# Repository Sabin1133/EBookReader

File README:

# Proiect Hardware cu ESP32-C6

## Descriere Generală

Acest proiect descrie funcționalitatea hardware a unui sistem bazat pe ESP32-C6, incluzând modulele, componentele și senzorii utilizați, interfețele de conectare, specificațiile de comunicație și calculele de consum de energie.

## Funcționalitate Hardware

### Module și Componente

* **ESP32-C6**: Microcontroller-ul principal, care oferă conectivitate Wi-Fi 6, Bluetooth LE 5.2 și suport pentru protocolul 802.15.4.
* **Senzor de temperatură și umiditate DHT11**: Utilizat pentru monitorizarea condițiilor ambientale.
* **Modul LED RGB**: Pentru afișarea vizuală a stărilor sistemului.
* **Buton tactil**: Pentru interacțiunea utilizatorului.

### Interfețe și Conectivitate

* Senzorul DHT11 este conectat la ESP32-C6 prin interfața GPIO.
* Modulul LED RGB este controlat prin pinii PWM ai ESP32-C6.
* Butonul tactil este conectat la un pin GPIO configurat ca intrare.
* ESP32-C6 comunică prin Wi-Fi pentru a trimite date către un server cloud.

### Specificații de Comunicație

* Wi-Fi 6 (802.11ax): Pentru conectivitate la rețeaua locală și internet.
* Bluetooth LE 5.2: Pentru comunicarea cu dispozitive mobile.
* Protocol 802.15.4: Pentru eventuale comunicații cu dispozitive Zigbee sau Thread.

### Procesare și Calcule

* ESP32-C6 procesează datele de la senzori și controlează modulul LED RGB.
* Se efectuează calcule pentru a converti datele brute ale senzorilor în unități de măsură relevante.
* Calcule de consum de energie.
    * ESP32-C6 în mod activ consumă în jur de 5mA
    * ESP32-C6 în mod sleep consumă în jur de 5µA
    * Senzorul de temperatură și umiditate DHT11 consumă aproximativ 2.5mA.

### Pini ESP32-C6 Utilizați

* **GPIO2 (DHT11 Data)**: Pin de intrare/ieșire pentru comunicarea cu senzorul DHT11.
    * Motiv: GPIO2 suportă interfața de comunicare necesară pentru DHT11.
* **GPIO4 (LED RGB Red)**: Pin PWM pentru controlul componentei roșii a LED-ului RGB.
    * Motiv: GPIO4 suportă PWM, necesar pentru controlul intensității LED-ului.
* **GPIO5 (LED RGB Green)**: Pin PWM pentru controlul componentei verzi a LED-ului RGB.
    * Motiv: GPIO5 suportă PWM, necesar pentru controlul intensității LED-ului.
* **GPIO6 (LED RGB Blue)**: Pin PWM pentru controlul componentei albastre a LED-ului RGB.
    * Motiv: GPIO6 suportă PWM, necesar pentru controlul intensității LED-ului.
* **GPIO7 (Buton tactil)**: Pin de intrare pentru citirea stării butonului tactil.
    * Motiv: GPIO7 poate fi configurat ca intrare digitală pentru a detecta starea butonului.

### Alte Informații Relevante

* Sistemul este alimentat de o baterie de 3.3V.
* Datele colectate sunt trimise către un server cloud pentru monitorizare și analiză.
* Codul sursă este disponibil în directorul `src`.

## Dependențe

* Biblioteca Adafruit DHT pentru comunicarea cu senzorul DHT11.
* Biblioteca Arduino pentru controlul pinilor GPIO și PWM.

## Instalare

1.  Clonați acest repository.
2.  Instalați bibliotecile necesare în Arduino IDE.
3.  Încărcați codul pe ESP32-C6.

## Utilizare

* Sistemul monitorizează temperatura și umiditatea și afișează valorile prin LED-ul RGB.
* Utilizatorul poate interacționa cu sistemul prin intermediul butonului tactil.

## Contribuție

Contribuțiile sunt binevenite! Vă rugăm să trimiteți pull requests sau să raportați probleme.

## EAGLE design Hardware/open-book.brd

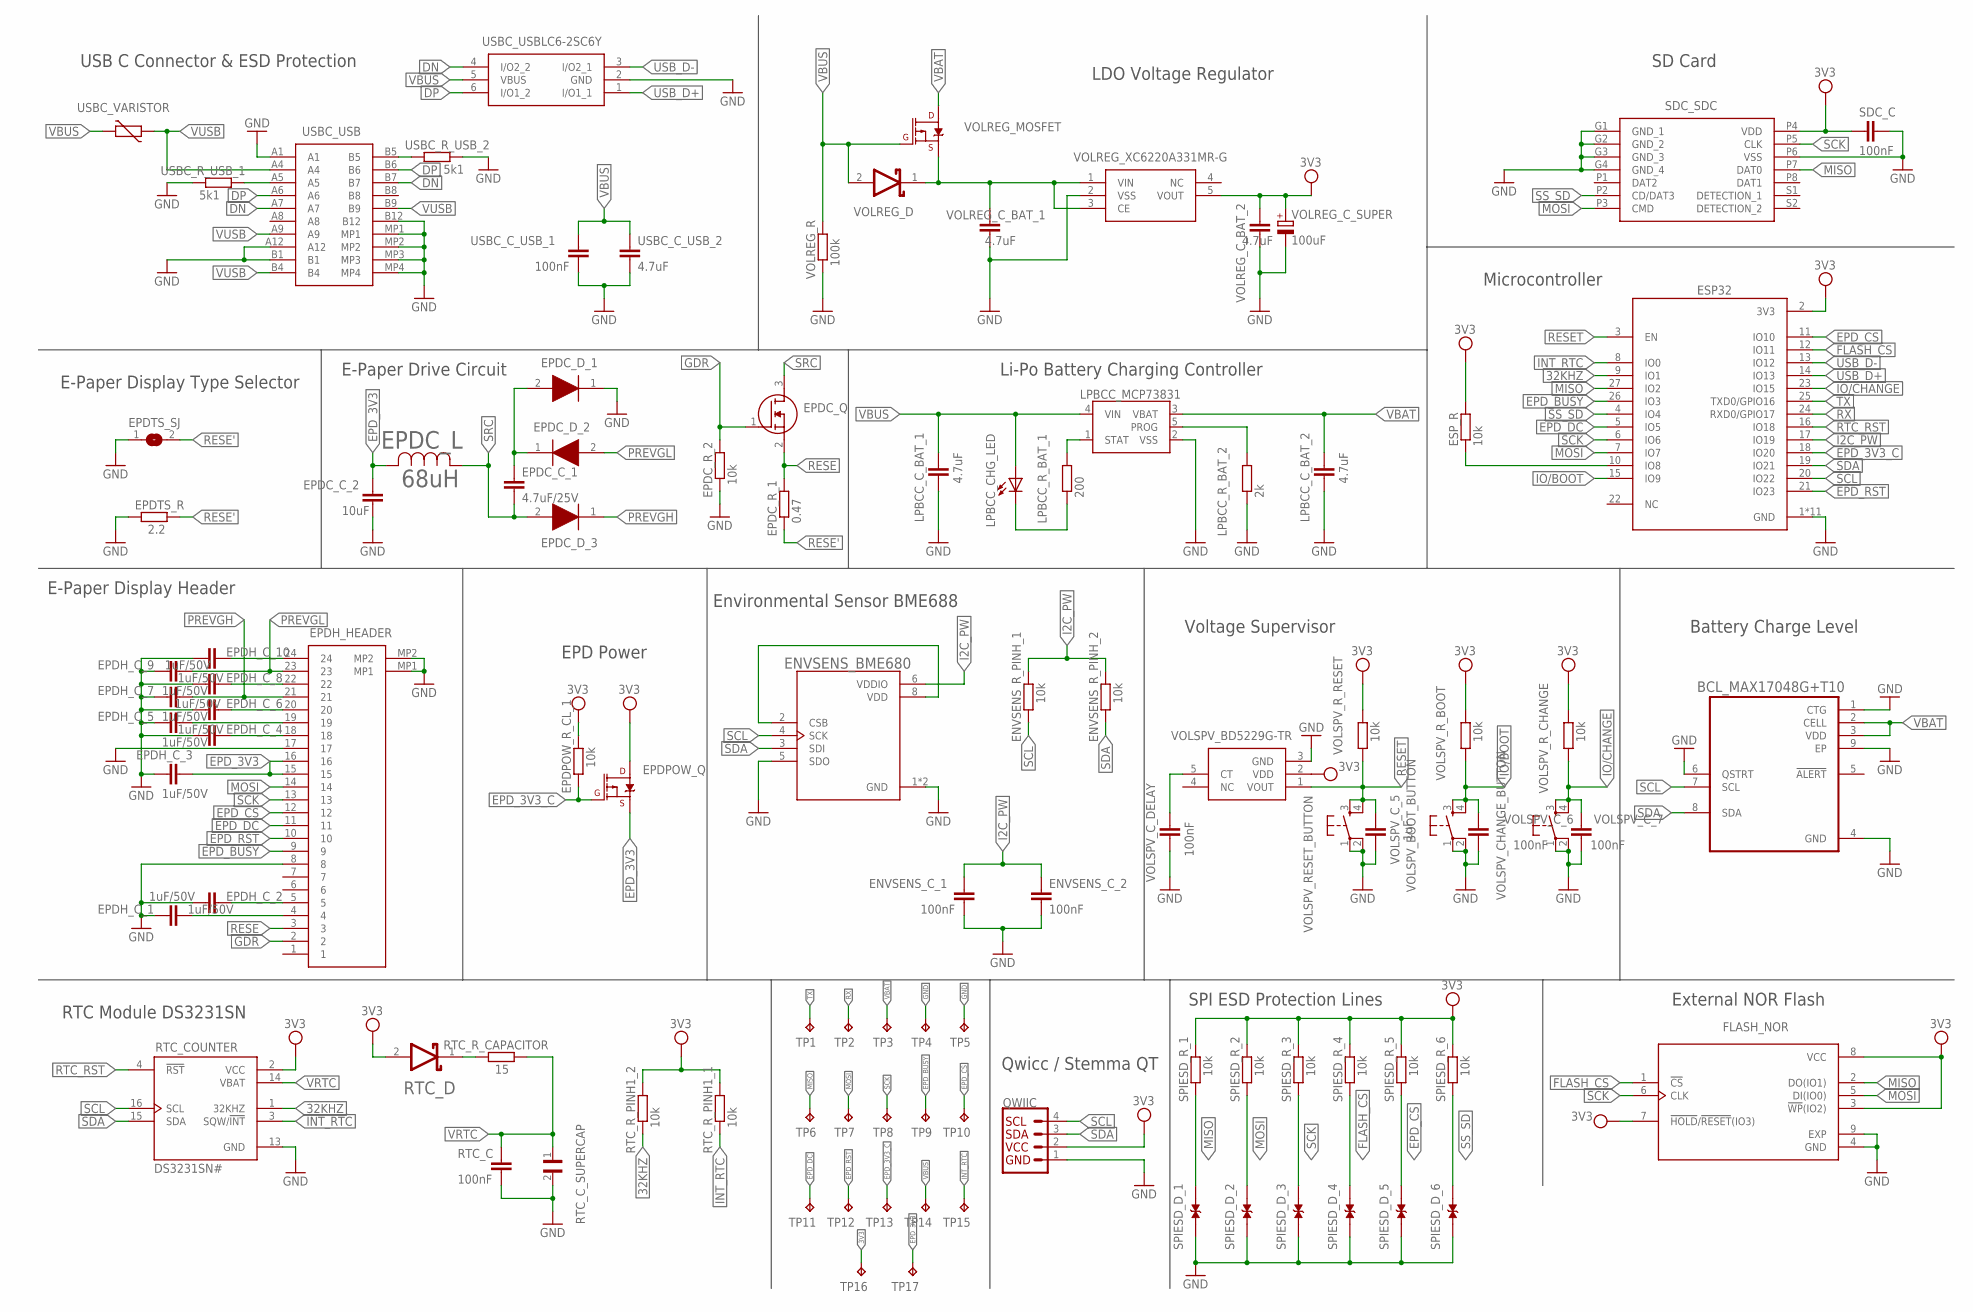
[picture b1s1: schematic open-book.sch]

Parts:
BCL_MAX17048G+T10: MAX17048G+T10; SON50P200X200X80-9N
ENVSENS_BME680: ESP32_WROVER_BME680_BME680; ESP32_WROVER_BME680_PSON80P300X300X100-8N
ENVSENS_C_1, ENVSENS_C_2: 100nF; EAGLE-LTSPICE_C0402
ENVSENS_R_PINH_1, ENVSENS_R_PINH_2: 10k; ESP32_WROVER_EAGLE-LTSPICE_R0402
EPDC_C_1: 4.7uF/25V; EAGLE-LTSPICE_C0402
EPDC_C_2: 10uF; EAGLE-LTSPICE_C0402
EPDC_D_1, EPDC_D_2, EPDC_D_3: MBR0530; SOD3716X135N
EPDC_L: 68uH; IND_4828-WE-TPC_WRE
EPDC_Q: SI1308EDL-T1-GE3; SOT65P210X110-3N
EPDC_R_1: 0.47; ESP32_WROVER_EAGLE-LTSPICE_R0402
EPDC_R_2: 10k; ESP32_WROVER_EAGLE-LTSPICE_R0402
EPDH_C_1, EPDH_C_2, EPDH_C_3, EPDH_C_4, EPDH_C_5, EPDH_C_6, EPDH_C_7, EPDH_C_8, EPDH_C_9, EPDH_C_10: 1uF/50V; EAGLE-LTSPICE_C0402
EPDH_HEADER: FH34SRJ-24S-0.5SH_99_; FH34SRJ24S05SH99
EPDPOW_Q: 20V/4.2A/52mΩ/1.4W; ESP32_WROVER_SPARKFUN-DISCRETESEMI_SOT23-3
EPDPOW_R_CL_1: 10k; ESP32_WROVER_EAGLE-LTSPICE_R0402
EPDTS_R: 2.2; ESP32_WROVER_EAGLE-LTSPICE_R0402
EPDTS_SJ: SJ
ESP32: ESP32-C6-WROOM-1-N8; XCVR_ESP32-C6-WROOM-1-N8
ESP_R: 10k; ESP32_WROVER_EAGLE-LTSPICE_R0402
FLASH_NOR: W25Q512JVEIQ; SON127P600X800X80-9N
LPBCC_CHG_LED: ADAFRUIT_LED; ADAFRUIT_CHIP-LED0603
LPBCC_C_BAT_1, LPBCC_C_BAT_2: 4.7uF; EAGLE-LTSPICE_C0402
LPBCC_MCP73831: ESP32_WROVER_SPARKFUN-IC-POWER_MCP73831; ESP32_WROVER_SPARKFUN-IC-POWER_SOT23-5
LPBCC_R_BAT_1: 200; ESP32_WROVER_EAGLE-LTSPICE_R0402
LPBCC_R_BAT_2: 2k; ESP32_WROVER_EAGLE-LTSPICE_R0402
QWIIC: QWIIC_RIGHT_ANGLE; JST04_1MM_RA
RTC_C: 100nF; EAGLE-LTSPICE_C0402
RTC_COUNTER: DS3231SN#; SOIC127P1032X265-16N
RTC_C_SUPERCAP: CPH3225A; CAPCP3225X100N
RTC_D: ESP32_WROVER_AVX---SD0805S020S1R0_AVX_SD0805S020S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; ESP32_WROVER_AVX---SD0805S020S1R0_AVX_SD0805S020S1R0_0
RTC_R_CAPACITOR: 15; ESP32_WROVER_EAGLE-LTSPICE_R0402
RTC_R_PINH1_1, RTC_R_PINH1_2: 10k; ESP32_WROVER_EAGLE-LTSPICE_R0402
SDC_C: 100nF; EAGLE-LTSPICE_C0402
SDC_SDC: 112A-TAAR-R03_ATTEND; 112ATAARR03ATTEND
SPIESD_D_1, SPIESD_D_2, SPIESD_D_3, SPIESD_D_4, SPIESD_D_5, SPIESD_D_6: PGB1010603MR; DIOC1608X36N
SPIESD_R_1, SPIESD_R_2, SPIESD_R_3, SPIESD_R_4, SPIESD_R_5, SPIESD_R_6: 10k; ESP32_WROVER_EAGLE-LTSPICE_R0402
TP1, TP2, TP3, TP4, TP5, TP6, TP7, TP8, TP9, TP10, TP11, TP12, TP13, TP14, TP15, TP16, TP17: TPTP20R; TP20R
USBC_C_USB_1: 100nF; EAGLE-LTSPICE_C0402
USBC_C_USB_2: 4.7uF; EAGLE-LTSPICE_C0402
USBC_R_USB_1, USBC_R_USB_2: 5k1; ESP32_WROVER_EAGLE-LTSPICE_R0402
USBC_USB: SAMACSYS_PARTS_USB4110-GF-A; SAMACSYS_PARTS_USB4110GFA
USBC_USBLC6-2SC6Y: USBLC6-2SC6Y; SOT95P280X145-6N
USBC_VARISTOR: ESP32C6_VARISTORCN1812; ESP32C6_VARISTOR_CT/CN1812
VOLREG_C_BAT_1, VOLREG_C_BAT_2: 4.7uF; EAGLE-LTSPICE_C0402
VOLREG_C_SUPER: 100uF; RCL_CT3528
VOLREG_D: ESP32_WROVER_AVX---SD0805S020S1R0_AVX_SD0805S020S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; ESP32_WROVER_AVX---SD0805S020S1R0_AVX_SD0805S020S1R0_0
VOLREG_MOSFET: 20V/4.2A/52mΩ/1.4W; ESP32_WROVER_SPARKFUN-DISCRETESEMI_SOT23-3
VOLREG_R: 100k; ESP32_WROVER_EAGLE-LTSPICE_R0402
VOLREG_XC6220A331MR-G: XC6220A331MR-G; SOT95P280X125-5N
VOLSPV_BD5229G-TR: BD5229G-TR; SOT95P280X125-5N
VOLSPV_BOOT_BUTTON: BUTTON_CUSYOMV1; MYBUTTON
VOLSPV_CHANGE_BUTTON: BUTTON_CUSYOMV1; MYBUTTON
VOLSPV_C_5: 1uF; EAGLE-LTSPICE_C0402
VOLSPV_C_6, VOLSPV_C_7: 100nF; EAGLE-LTSPICE_C0402
VOLSPV_C_DELAY: 100nF; EAGLE-LTSPICE_C0402
VOLSPV_RESET_BUTTON: BUTTON_CUSYOMV1; MYBUTTON
VOLSPV_R_BOOT: 10k; ESP32_WROVER_EAGLE-LTSPICE_R0402
VOLSPV_R_CHANGE: 10k; ESP32_WROVER_EAGLE-LTSPICE_R0402
VOLSPV_R_RESET: 10k; ESP32_WROVER_EAGLE-LTSPICE_R0402

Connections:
3V3: EPDPOW_Q.3 (D), EPDPOW_R_CL_1.2, ESP32.2 (3V3), ESP_R.2, FLASH_NOR.3 (!WP!(IO2)), FLASH_NOR.7 (!HOLD!/!RESET!(IO3)), FLASH_NOR.8 (VCC), QWIIC.2, RTC_COUNTER.2 (VCC), RTC_D.2 (ANODE), RTC_R_PINH1_1.2, RTC_R_PINH1_2.2, SDC_C.1, SDC_SDC.P4 (VDD), SPIESD_R_1.2, SPIESD_R_2.2, SPIESD_R_3.2, SPIESD_R_4.2, SPIESD_R_5.2, SPIESD_R_6.2, TP16.TP, VOLREG_C_BAT_2.1, VOLREG_C_SUPER.+, VOLREG_XC6220A331MR-G.5 (VOUT), VOLSPV_BD5229G-TR.2 (VDD), VOLSPV_R_BOOT.2, VOLSPV_R_CHANGE.2, VOLSPV_R_RESET.2
32KHZ: ESP32.9 (IO1), RTC_COUNTER.1 (32KHZ), RTC_R_PINH1_2.1
DN: USBC_USB.A7, USBC_USB.B7, USBC_USBLC6-2SC6Y.4 (I/O2_2)
DP: USBC_USB.A6, USBC_USB.B6, USBC_USBLC6-2SC6Y.6 (I/O1_2)
EPD_3V3: EPDC_C_2.1, EPDC_L.2, EPDH_C_3.2, EPDH_HEADER.15, EPDH_HEADER.16, EPDPOW_Q.2 (S), TP17.TP
EPD_3V3_C: EPDPOW_Q.1 (G), EPDPOW_R_CL_1.1, ESP32.18 (IO20), TP13.TP
EPD_BUSY: EPDH_HEADER.9, ESP32.26 (IO3), TP9.TP
EPD_CS: EPDH_HEADER.12, ESP32.11 (IO10), SPIESD_D_5.2, SPIESD_R_5.1, TP10.TP
EPD_DC: EPDH_HEADER.11, ESP32.5 (IO5), TP11.TP
EPD_RST: EPDH_HEADER.10, ESP32.21 (IO23), TP12.TP
FLASH_CS: ESP32.12 (IO11), FLASH_NOR.1 (!CS), SPIESD_D_4.2, SPIESD_R_4.1
GDR: EPDC_Q.1 (G), EPDC_R_2.2, EPDH_HEADER.2
GND: BCL_MAX17048G+T10.1 (CTG), BCL_MAX17048G+T10.4 (GND), BCL_MAX17048G+T10.6 (QSTRT), BCL_MAX17048G+T10.9 (EP), ENVSENS_BME680.1 (GND), ENVSENS_BME680.5 (SDO), ENVSENS_BME680.7 (GND), ENVSENS_C_1.2, ENVSENS_C_2.2, EPDC_C_2.2, EPDC_D_1.1 (K), EPDC_R_2.1, EPDH_C_1.1, EPDH_C_2.1, EPDH_C_3.1, EPDH_C_4.1, EPDH_C_5.1, EPDH_C_6.1, EPDH_C_7.1, EPDH_C_8.1, EPDH_C_9.1, EPDH_C_10.1, EPDH_HEADER.8, EPDH_HEADER.17, EPDH_HEADER.MP1, EPDH_HEADER.MP2, EPDTS_R.1, EPDTS_SJ.1, ESP32.1 (GND), ESP32.28 (GND), ESP32.29_1 (GND), ESP32.29_2 (GND), ESP32.29_3 (GND), ESP32.29_4 (GND), ESP32.29_5 (GND), ESP32.29_6 (GND), ESP32.29_7 (GND), ESP32.29_8 (GND), ESP32.29_9 (GND), FLASH_NOR.4 (GND), FLASH_NOR.9 (EXP), LPBCC_C_BAT_1.2, LPBCC_C_BAT_2.2, LPBCC_MCP73831.2 (VSS), LPBCC_R_BAT_2.1, QWIIC.1, RTC_C.2, RTC_COUNTER.13 (GND), RTC_C_SUPERCAP.2, SDC_C.2, SDC_SDC.G1 (GND_1), SDC_SDC.G2 (GND_2), SDC_SDC.G3 (GND_3), SDC_SDC.G4 (GND_4), SDC_SDC.P6 (VSS), SPIESD_D_1.1, SPIESD_D_2.1, SPIESD_D_3.1, SPIESD_D_4.1, SPIESD_D_5.1, SPIESD_D_6.1, TP4.TP, TP5.TP, USBC_C_USB_1.2, USBC_C_USB_2.2, USBC_R_USB_1.1, USBC_R_USB_2.2, USBC_USB.A1, USBC_USB.A12, USBC_USB.B1, USBC_USB.B12, USBC_USB.MP1, USBC_USB.MP2, USBC_USB.MP3, USBC_USB.MP4, USBC_USBLC6-2SC6Y.2 (GND), VOLREG_C_BAT_1.2, VOLREG_C_BAT_2.2, VOLREG_C_SUPER.-, VOLREG_R.1, VOLREG_XC6220A331MR-G.2 (VSS), VOLSPV_BD5229G-TR.3 (GND), VOLSPV_BOOT_BUTTON.1, VOLSPV_BOOT_BUTTON.2, VOLSPV_CHANGE_BUTTON.1, VOLSPV_CHANGE_BUTTON.2, VOLSPV_C_5.2, VOLSPV_C_6.2, VOLSPV_C_7.2, VOLSPV_C_DELAY.2, VOLSPV_RESET_BUTTON.1, VOLSPV_RESET_BUTTON.2
I2C_PW: ENVSENS_BME680.6 (VDDIO), ENVSENS_C_1.1, ENVSENS_C_2.1, ENVSENS_R_PINH_1.2, ENVSENS_R_PINH_2.2, ESP32.17 (IO19)
INT_RTC: ESP32.8 (IO0), RTC_COUNTER.3 (SQW/!INT), RTC_R_PINH1_1.1, TP15.TP
IO/BOOT: ESP32.15 (IO9), VOLSPV_BOOT_BUTTON.3, VOLSPV_BOOT_BUTTON.4, VOLSPV_C_6.1, VOLSPV_R_BOOT.1
IO/CHANGE: ESP32.23 (IO15), VOLSPV_CHANGE_BUTTON.3, VOLSPV_CHANGE_BUTTON.4, VOLSPV_C_7.1, VOLSPV_R_CHANGE.1
MISO: ESP32.27 (IO2), FLASH_NOR.2 (DO(IO1)), SDC_SDC.P7 (DAT0), SPIESD_D_1.2, SPIESD_R_1.1, TP6.TP
MOSI: EPDH_HEADER.14, ESP32.7 (IO7), FLASH_NOR.5 (DI(IO0)), SDC_SDC.P3 (CMD), SPIESD_D_2.2, SPIESD_R_2.1, TP7.TP
unnamed: VOLREG_C_BAT_1.1, VOLREG_D.1 (CATHODE), VOLREG_MOSFET.2 (S), VOLREG_XC6220A331MR-G.1 (VIN), VOLREG_XC6220A331MR-G.3 (CE)
unnamed: VOLSPV_BD5229G-TR.5 (CT), VOLSPV_C_DELAY.1
unnamed: LPBCC_MCP73831.1 (STAT), LPBCC_R_BAT_1.2
unnamed: LPBCC_CHG_LED.C, LPBCC_R_BAT_1.1
unnamed: ESP32.10 (IO8), ESP_R.1
unnamed: LPBCC_MCP73831.5 (PROG), LPBCC_R_BAT_2.2
unnamed: USBC_R_USB_2.1, USBC_USB.B5
unnamed: EPDH_C_10.2, EPDH_HEADER.24
unnamed: EPDC_C_1.1, EPDC_D_1.2 (A), EPDC_D_2.1 (K)
unnamed: EPDH_C_8.2, EPDH_HEADER.22
unnamed: ENVSENS_BME680.2 (CSB), ENVSENS_BME680.8 (VDD)
unnamed: RTC_D.1 (CATHODE), RTC_R_CAPACITOR.1
unnamed: EPDH_C_6.2, EPDH_HEADER.20
unnamed: EPDH_C_5.2, EPDH_HEADER.19
unnamed: USBC_R_USB_1.2, USBC_USB.A5
unnamed: EPDH_C_4.2, EPDH_HEADER.18
unnamed: EPDH_C_2.2, EPDH_HEADER.5
unnamed: EPDH_C_1.2, EPDH_HEADER.4
PREVGH: EPDC_D_3.1 (K), EPDH_C_7.2, EPDH_HEADER.21
PREVGL: EPDC_D_2.2 (A), EPDH_C_9.2, EPDH_HEADER.23
RESE: EPDC_Q.2 (S), EPDC_R_1.2, EPDH_HEADER.3
RESE': EPDC_R_1.1, EPDTS_R.2, EPDTS_SJ.2
RESET: ESP32.3 (EN), VOLSPV_BD5229G-TR.1 (VOUT), VOLSPV_C_5.1, VOLSPV_RESET_BUTTON.3, VOLSPV_RESET_BUTTON.4, VOLSPV_R_RESET.1
RTC_RST: ESP32.16 (IO18), RTC_COUNTER.4 (!RST)
RX: ESP32.24 (RXD0/GPIO17), TP2.TP
SCK: EPDH_HEADER.13, ESP32.6 (IO6), FLASH_NOR.6 (CLK), SDC_SDC.P5 (CLK), SPIESD_D_3.2, SPIESD_R_3.1, TP8.TP
SCL: BCL_MAX17048G+T10.7 (SCL), ENVSENS_BME680.4 (SCK), ENVSENS_R_PINH_1.1, ESP32.20 (IO22), QWIIC.4, RTC_COUNTER.16 (SCL)
SDA: BCL_MAX17048G+T10.8 (SDA), ENVSENS_BME680.3 (SDI), ENVSENS_R_PINH_2.1, ESP32.19 (IO21), QWIIC.3, RTC_COUNTER.15 (SDA)
SRC: EPDC_C_1.2, EPDC_D_3.2 (A), EPDC_L.1, EPDC_Q.3 (D)
SS_SD: ESP32.4 (IO4), SDC_SDC.P2 (CD/DAT3), SPIESD_D_6.2, SPIESD_R_6.1
TX: ESP32.25 (TXD0/GPIO16), TP1.TP
USB_D+: ESP32.14 (IO13), USBC_USBLC6-2SC6Y.1 (I/O1_1)
USB_D-: ESP32.13 (IO12), USBC_USBLC6-2SC6Y.3 (I/O2_1)
VBAT: BCL_MAX17048G+T10.2 (CELL), BCL_MAX17048G+T10.3 (VDD), LPBCC_C_BAT_2.1, LPBCC_MCP73831.3 (VBAT), TP3.TP, VOLREG_MOSFET.3 (D)
VBUS: LPBCC_CHG_LED.A, LPBCC_C_BAT_1.1, LPBCC_MCP73831.4 (VIN), TP14.TP, USBC_C_USB_1.1, USBC_C_USB_2.1, USBC_USBLC6-2SC6Y.5 (VBUS), USBC_VARISTOR.2, VOLREG_D.2 (ANODE), VOLREG_MOSFET.1 (G), VOLREG_R.2
VRTC: RTC_C.1, RTC_COUNTER.14 (VBAT), RTC_C_SUPERCAP.1, RTC_R_CAPACITOR.2
VUSB: USBC_USB.A4, USBC_USB.A9, USBC_USB.B4, USBC_USB.B9, USBC_VARISTOR.1

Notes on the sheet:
EPD Power
Voltage Supervisor
LDO Voltage Regulator
Li-Po Battery Charging Controller
Battery Charge Level
Microcontroller
Qwicc / Stemma QT
SPI ESD Protection Lines
Environmental Sensor BME688
RTC Module DS3231SN
USB C Connector & ESD Protection
External NOR Flash
SD Card
E-Paper Drive Circuit
E-Paper Display Type Selector
E-Paper Display Header

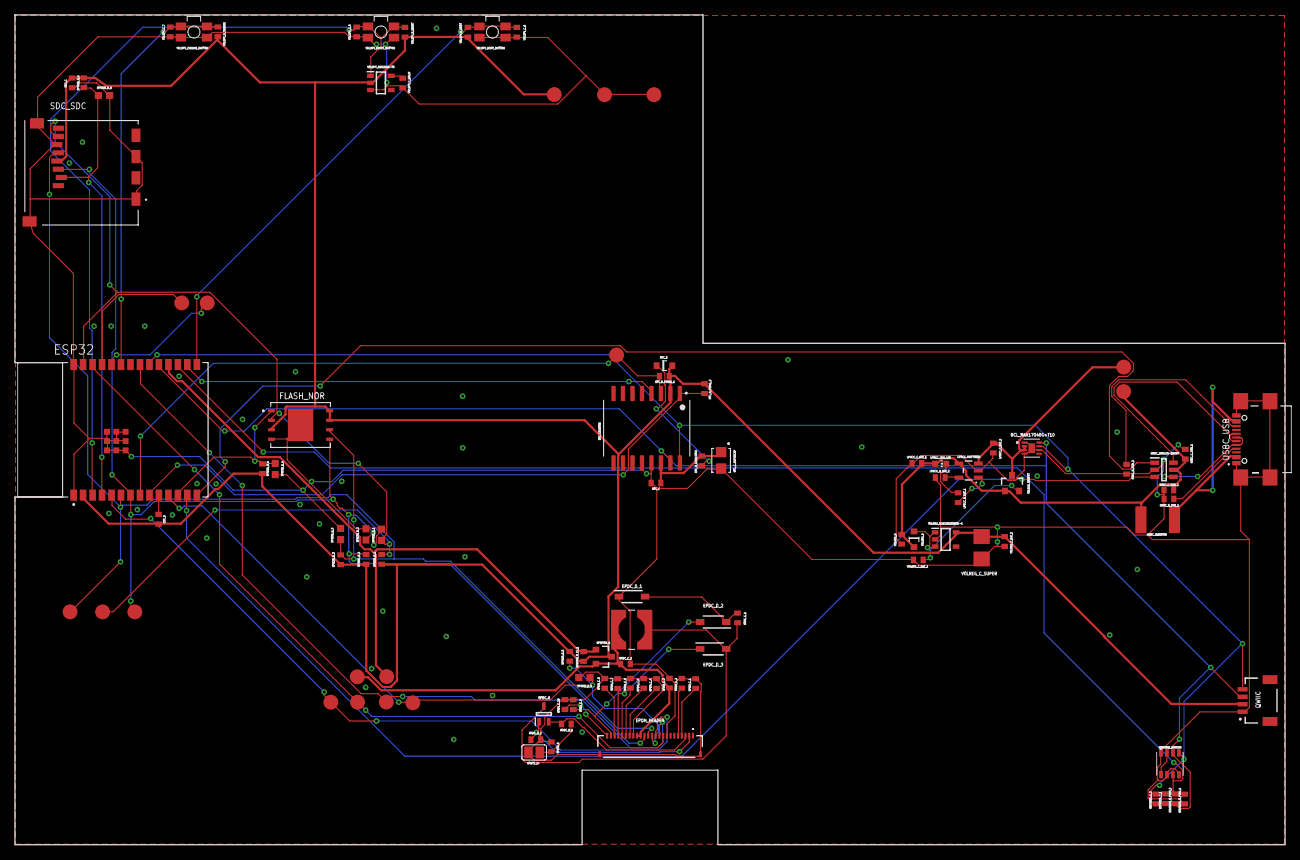
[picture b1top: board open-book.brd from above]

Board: 2 copper layers, 170.2 x 111.2 mm, 103 parts (0 on the bottom side), 56 nets.

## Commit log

2025-04-06 Create LICENSE
    Added LICENSE file
2025-04-06 Added files
2025-04-06 Added README file
2025-04-07 Forgot file extension
2025-04-07 Forgot to rename files
2025-04-11 Fixed issue #4 by placing text on info layer
2025-04-11 Fixed issue #1 by fixing VUSB connection
2025-04-11 Fixed issue #2 by aligning components' names
2025-04-11 Fixed issue #5 by the improving the visual aspect and adding more visual details
2025-04-14 Small fix
2025-04-14 Another quick fix (Changed 3d wires and PCB extra names)
